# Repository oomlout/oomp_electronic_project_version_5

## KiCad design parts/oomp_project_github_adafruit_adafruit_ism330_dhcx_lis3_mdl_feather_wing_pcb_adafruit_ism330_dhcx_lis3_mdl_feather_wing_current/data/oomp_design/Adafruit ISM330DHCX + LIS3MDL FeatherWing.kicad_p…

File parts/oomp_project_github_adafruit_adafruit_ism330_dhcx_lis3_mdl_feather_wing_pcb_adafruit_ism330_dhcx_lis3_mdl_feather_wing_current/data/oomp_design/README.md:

# OOMP KiCad design copy

Open `Adafruit ISM330DHCX + LIS3MDL FeatherWing.kicad_pro` (or the `.kicad_pcb` / `.kicad_sch`) in KiCad. Local OOMP libraries are under `libraries/`. Original inputs are preserved in [../original/](../original/).

Only verified unchanged installed KiCad defaults were renamed. Modified, custom, unmatched and unavailable items remain unchanged. Soldering variants are never swapped during conversion. Existing pad coordinates, nets and UUIDs are preserved.

See [conversion_report.yaml](conversion_report.yaml) for every conversion and skip. Copy this directory before editing; regeneration refuses to overwrite edited design files.

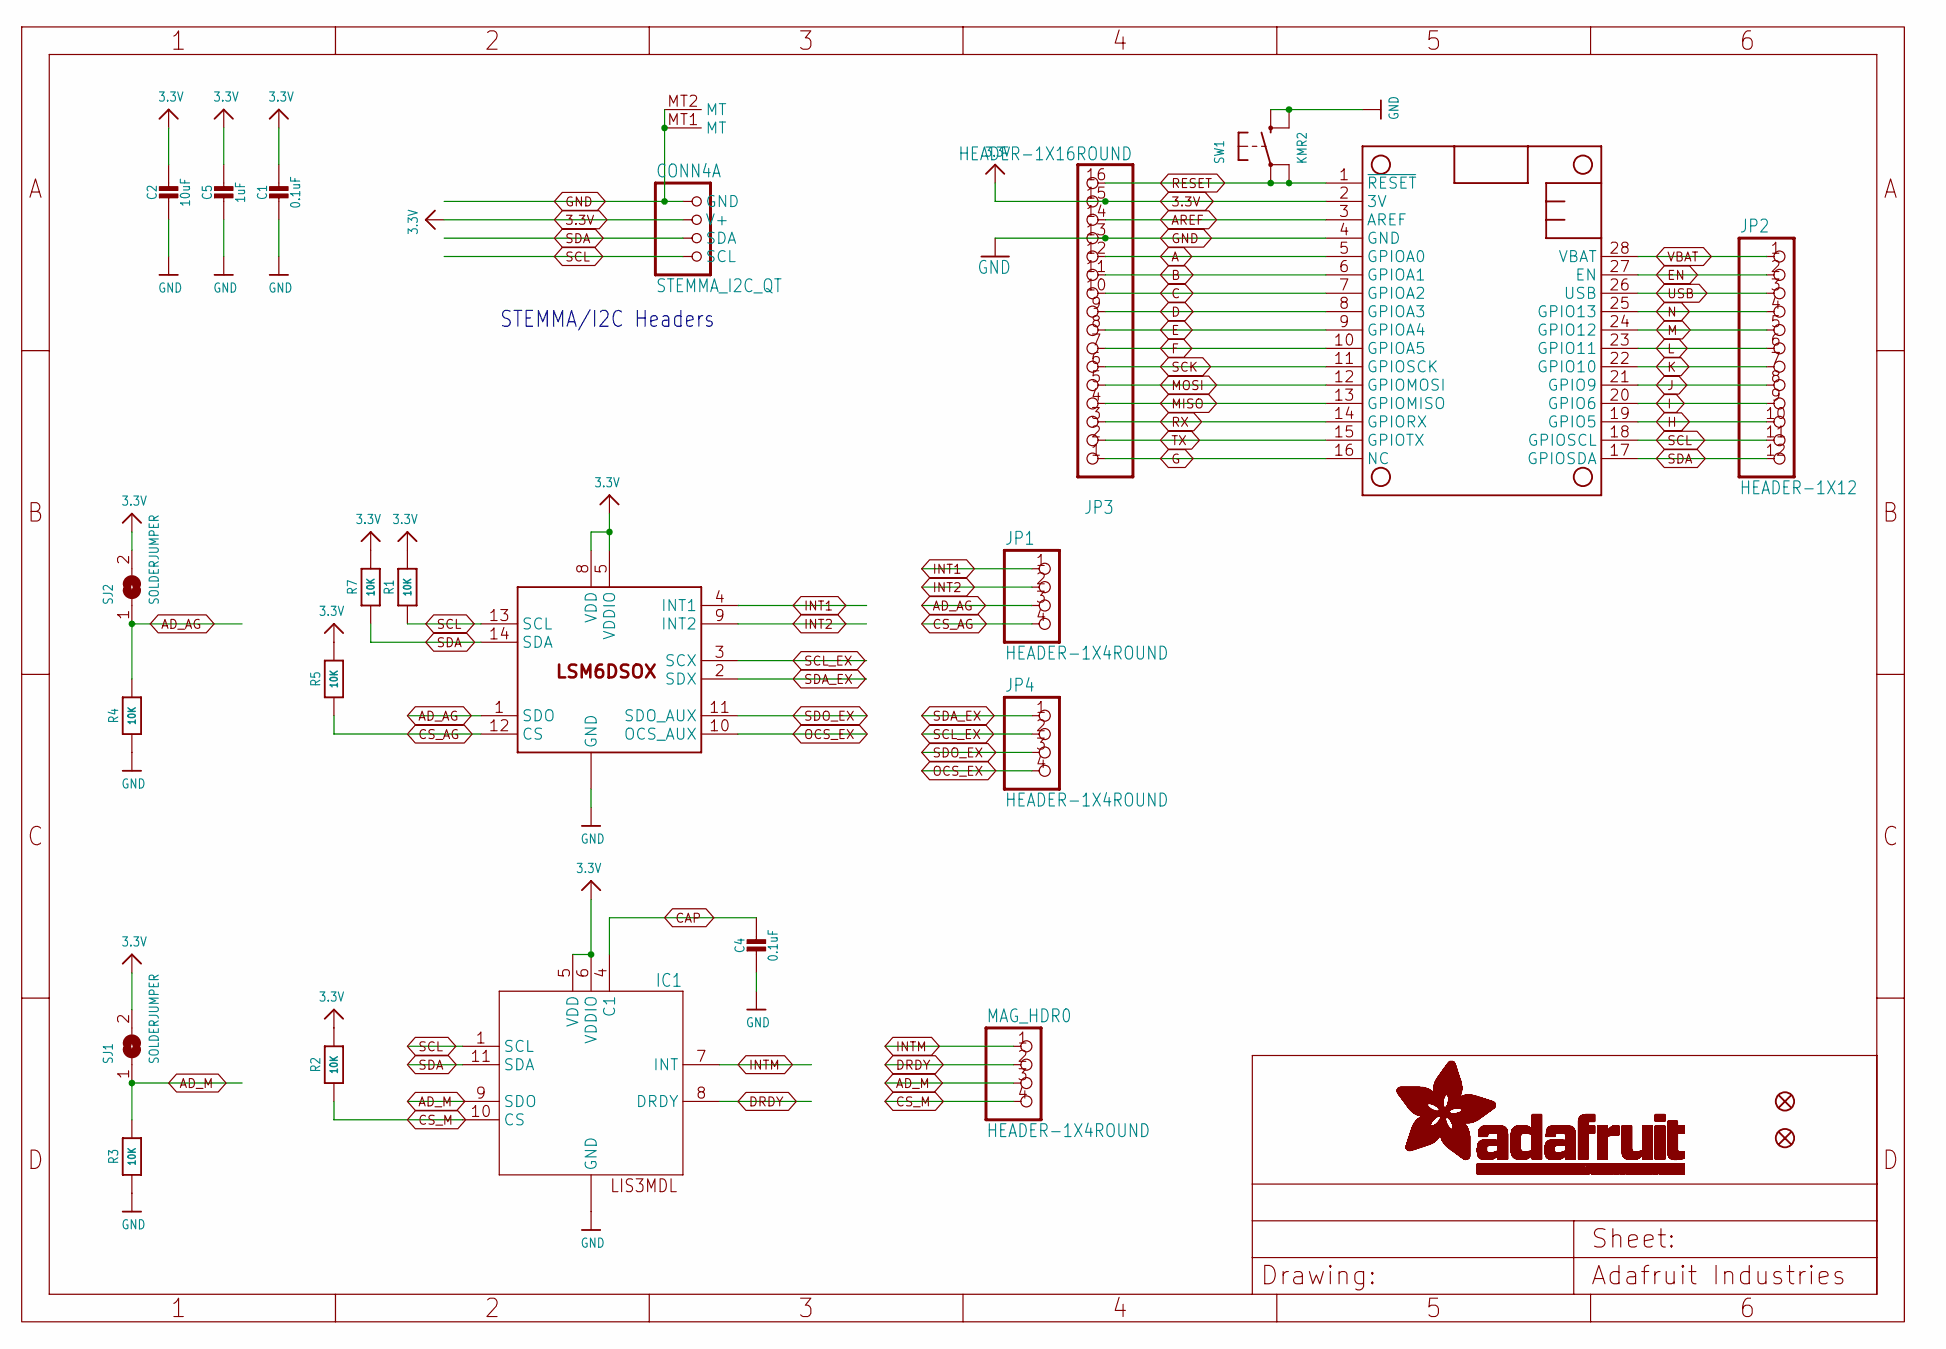
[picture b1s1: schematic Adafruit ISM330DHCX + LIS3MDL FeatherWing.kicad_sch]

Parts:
C1, C4: 0.1uF; 0603-NO
C2: 10uF; 0805-NO
C5: 1uF; 0603-NO
CONN4: STEMMA_I2C_QT; JST_SH4
FID1, FID2: FIDUCIAL_1MM
IC1: LIS3MDL; LGA12_2X2MM
JP1, JP4: HEADER-1X4ROUND; 1X04_ROUND
JP2: HEADER-1X12; 1X12_ROUND
JP3: HEADER-1X16ROUND; 1X16_ROUND
MAG_HDR0: HEADER-1X4ROUND; 1X04_ROUND
MS1: FEATHERWING
R1, R2, R3, R4, R5, R7: 10K; 0603-NO
SJ1, SJ2: SOLDERJUMPER; SOLDERJUMPER_ARROW_NOPASTE
SW1: KMR2; BTN_KMR2_4.6X2.8
U$35: LSM6DSOX; LGA-14L

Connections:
3.3V: C1.1, C2.1, C5.1, CONN4.2 (V+), IC1.5 (VDD), IC1.6 (VDDIO), JP3.15, MS1.2 (3V), R1.2, R2.2, R5.2, R7.2, SJ1.2, SJ2.2, U$35.5 (VDDIO), U$35.8 (VDD)
A: JP3.12, MS1.5 (GPIOA0)
AD_AG: JP1.3, R4.2, SJ2.1, U$35.1 (SDO)
AD_M: IC1.9 (SDO), MAG_HDR0.3, R3.2, SJ1.1
AREF: JP3.14, MS1.3 (AREF)
B: JP3.11, MS1.6 (GPIOA1)
C: JP3.10, MS1.7 (GPIOA2)
CAP: C4.1, IC1.4 (C1)
CS_AG: JP1.4, R5.1, U$35.12 (CS)
CS_M: IC1.10 (CS), MAG_HDR0.4, R2.1
D: JP3.9, MS1.8 (GPIOA3)
DRDY: IC1.8 (DRDY), MAG_HDR0.2
E: JP3.8, MS1.9 (GPIOA4)
EN: JP2.2, MS1.27 (EN)
F: JP3.7, MS1.10 (GPIOA5)
G: JP3.1, MS1.16 (NC)
GND: C1.2, C2.2, C4.2, C5.2, CONN4.1 (GND), CONN4.MT1 (MT), CONN4.MT2 (MT), IC1.2 (GND), IC1.3 (GND), IC1.12 (GND), JP3.13, MS1.4 (GND), R3.1, R4.1, SW1.B (S), SW1.B' (S1), U$35.6 (GND), U$35.7 (GND)
H: JP2.10, MS1.19 (GPIO5)
I: JP2.9, MS1.20 (GPIO6)
INT1: JP1.1, U$35.4 (INT1)
INT2: JP1.2, U$35.9 (INT2)
INTM: IC1.7 (INT), MAG_HDR0.1
J: JP2.8, MS1.21 (GPIO9)
K: JP2.7, MS1.22 (GPIO10)
L: JP2.6, MS1.23 (GPIO11)
M: JP2.5, MS1.24 (GPIO12)
MISO: JP3.4, MS1.13 (GPIOMISO)
MOSI: JP3.5, MS1.12 (GPIOMOSI)
N: JP2.4, MS1.25 (GPIO13)
OCS_EX: JP4.4, U$35.10 (OCS_AUX)
RESET: JP3.16, MS1.1 (~RESET), SW1.A, SW1.A' (P1)
RX: JP3.3, MS1.14 (GPIORX)
SCK: JP3.6, MS1.11 (GPIOSCK)
SCL: CONN4.4 (SCL), IC1.1 (SCL), JP2.11, MS1.18 (GPIOSCL), R1.1, U$35.13 (SCL)
SCL_EX: JP4.2, U$35.3 (SCX)
SDA: CONN4.3 (SDA), IC1.11 (SDA), JP2.12, MS1.17 (GPIOSDA), R7.1, U$35.14 (SDA)
SDA_EX: JP4.1, U$35.2 (SDX)
SDO_EX: JP4.3, U$35.11 (SDO_AUX)
TX: JP3.2, MS1.15 (GPIOTX)
USB: JP2.3, MS1.26 (USB)
VBAT: JP2.1, MS1.28 (VBAT)

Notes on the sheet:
STEMMA/I2C Headers

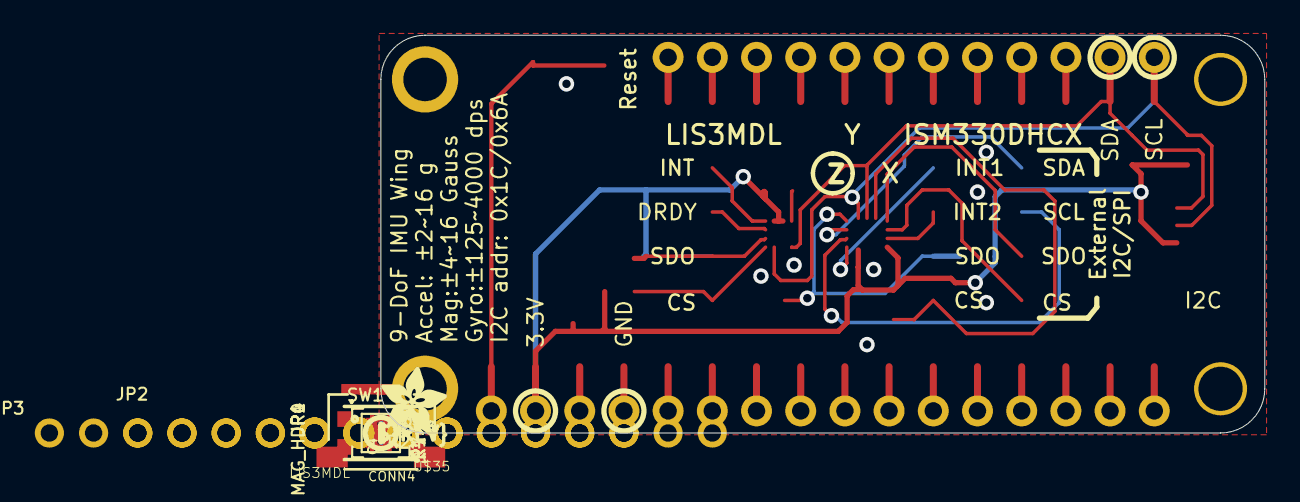
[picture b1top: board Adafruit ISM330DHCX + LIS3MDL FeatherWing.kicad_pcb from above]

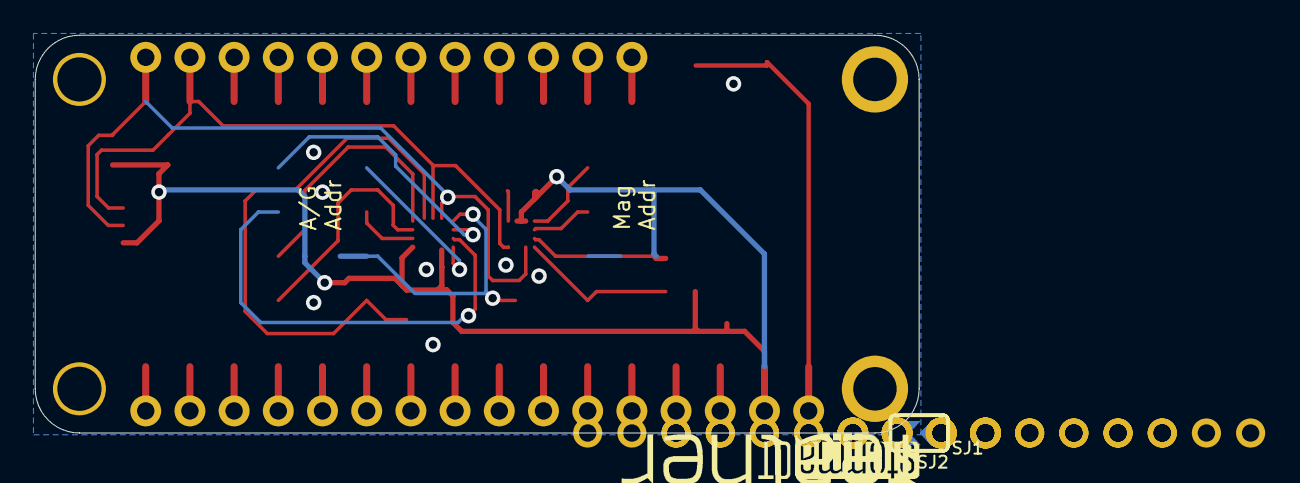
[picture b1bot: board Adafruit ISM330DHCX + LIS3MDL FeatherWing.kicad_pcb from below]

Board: 2 copper layers, 50.8 x 22.9 mm, 28 parts (4 on the bottom side), 41 nets.

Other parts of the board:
U$13: FEATHERLOGO_MED
U$31: STEMMAQT
U$50: ADAFRUIT_3.5MM
U$51: PCBFEAT-REV-040

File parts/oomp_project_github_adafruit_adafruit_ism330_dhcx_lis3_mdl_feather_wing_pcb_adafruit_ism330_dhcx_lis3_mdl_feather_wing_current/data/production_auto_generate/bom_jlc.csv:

Comment,Designator,Footprint,LCSC Part #
,"JP1,JP4,MAG_HDR0",Adafruit ISM330DHCX + LIS3MDL FeatherWing-import-fps:1X04_ROUND,C42431795
,JP2,Adafruit ISM330DHCX + LIS3MDL FeatherWing-import-fps:1X12_ROUND,C7501588
,JP3,Adafruit ISM330DHCX + LIS3MDL FeatherWing-import-fps:1X16_ROUND,C7501270
,U$50,Adafruit ISM330DHCX + LIS3MDL FeatherWing-import-fps:ADAFRUIT_3.5MM,
,U$13,Adafruit ISM330DHCX + LIS3MDL FeatherWing-import-fps:FEATHERLOGO_MED,
,U$51,Adafruit ISM330DHCX + LIS3MDL FeatherWing-import-fps:PCBFEAT-REV-040,
,U$31,Adafruit ISM330DHCX + LIS3MDL FeatherWing-import-fps:STEMMAQT,
0.1uF,"C1,C4",Adafruit ISM330DHCX + LIS3MDL FeatherWing-import-fps:0603-NO,C14663
10K,"R1,R2,R3,R4,R5,R7",Adafruit ISM330DHCX + LIS3MDL FeatherWing-import-fps:0603-NO,C98220
10uF,C2,Adafruit ISM330DHCX + LIS3MDL FeatherWing-import-fps:0805-NO,
1uF,C5,Adafruit ISM330DHCX + LIS3MDL FeatherWing-import-fps:0603-NO,C5673
FEATHERWING,MS1,Adafruit ISM330DHCX + LIS3MDL FeatherWing-import-fps:FEATHERWING,
KMR2,SW1,Adafruit ISM330DHCX + LIS3MDL FeatherWing-import-fps:BTN_KMR2_4.6X2.8,
LIS3MDL,IC1,Adafruit ISM330DHCX + LIS3MDL FeatherWing-import-fps:LGA12_2X2MM,
LSM6DSOX,U$35,Adafruit ISM330DHCX + LIS3MDL FeatherWing-import-fps:LGA-14L,
STEMMA_I2C_QT,CONN4,Adafruit ISM330DHCX + LIS3MDL FeatherWing-import-fps:JST_SH4,C160404

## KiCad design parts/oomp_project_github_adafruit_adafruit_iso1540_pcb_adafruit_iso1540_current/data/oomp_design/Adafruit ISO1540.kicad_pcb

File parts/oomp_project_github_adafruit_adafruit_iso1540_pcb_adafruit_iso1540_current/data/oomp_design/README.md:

# OOMP KiCad design copy

Open `Adafruit ISO1540.kicad_pro` (or the `.kicad_pcb` / `.kicad_sch`) in KiCad. Local OOMP libraries are under `libraries/`. Original inputs are preserved in [../original/](../original/).

Only verified unchanged installed KiCad defaults were renamed. Modified, custom, unmatched and unavailable items remain unchanged. Soldering variants are never swapped during conversion. Existing pad coordinates, nets and UUIDs are preserved.

See [conversion_report.yaml](conversion_report.yaml) for every conversion and skip. Copy this directory before editing; regeneration refuses to overwrite edited design files.

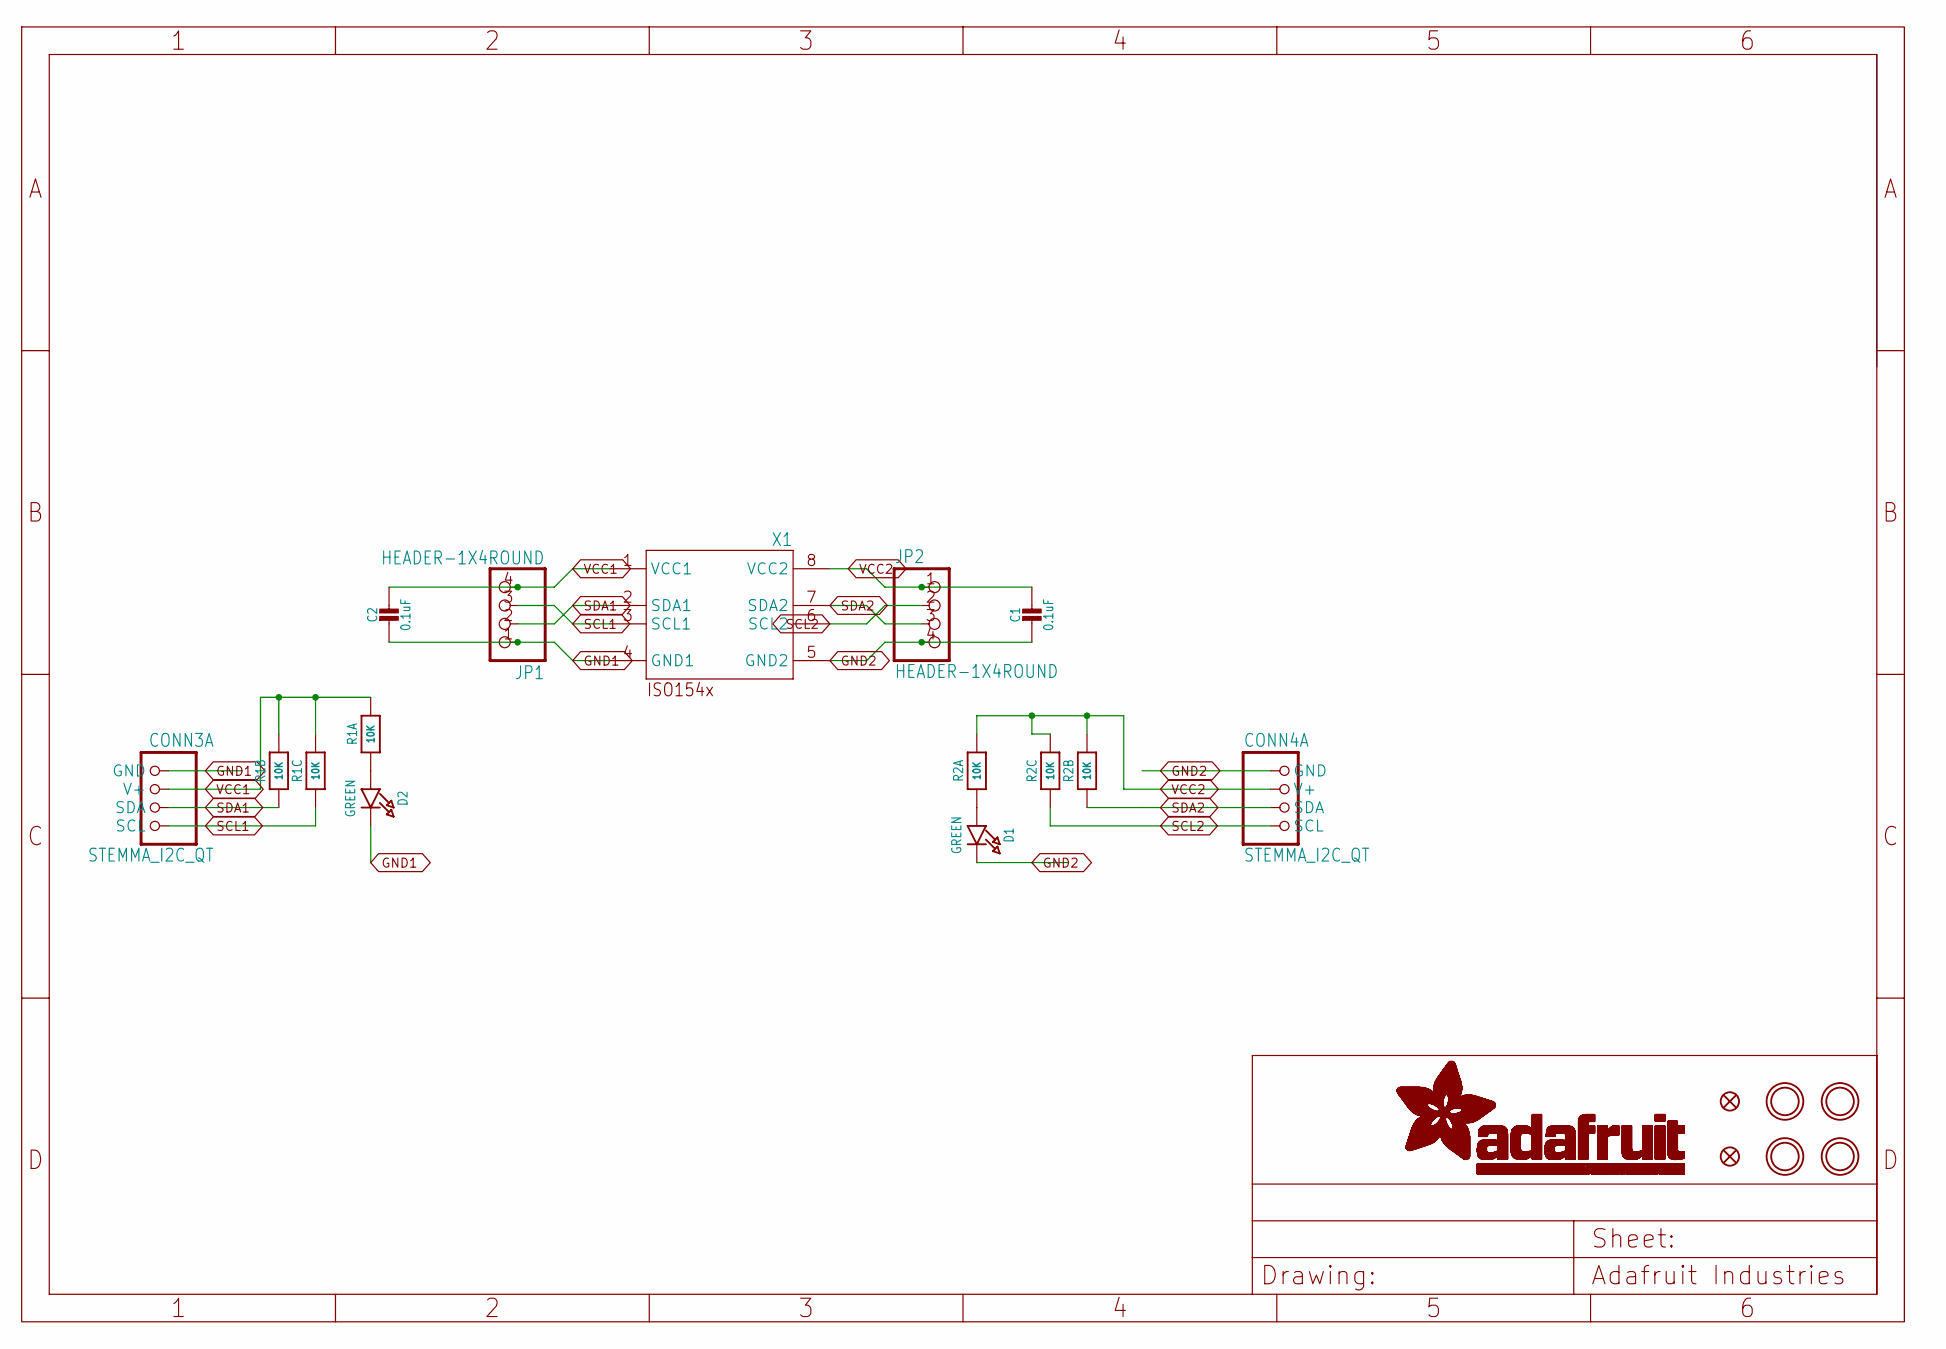
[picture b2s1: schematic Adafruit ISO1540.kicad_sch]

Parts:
C1, C2: 0.1uF; 0603-NO
CONN3, CONN4: STEMMA_I2C_QT; JST_SH4
D1, D2: GREEN; CHIPLED_0603_NOOUTLINE
FID3, FID4: FIDUCIAL_1MM
JP1, JP2: HEADER-1X4ROUND; 1X04_ROUND
R1, R2: 10K; RESPACK_4X0603
U$1, U$17, U$19, U$21: MOUNTINGHOLE2.5; MOUNTINGHOLE_2.5_PLATED
X1: ISO154X; SOIC8_150MIL

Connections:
GND1: C2.2, CONN3.1 (GND), D2.C, JP1.1, X1.4 (GND1)
GND2: C1.2, CONN4.1 (GND), D1.C, JP2.4, X1.5 (GND2)
unnamed: D2.A, R1.1
unnamed: D1.A, R2.1
SCL1: CONN3.4 (SCL), JP1.3, R1.3 (1), X1.3 (SCL1)
SCL2: CONN4.4 (SCL), JP2.2, R2.3 (1), X1.6 (SCL2)
SDA1: CONN3.3 (SDA), JP1.2, R1.2 (1), X1.2 (SDA1)
SDA2: CONN4.3 (SDA), JP2.3, R2.2 (1), X1.7 (SDA2)
VCC1: C2.1, CONN3.2 (V+), JP1.4, R1.6 (2), R1.7 (2), R1.8 (2), X1.1 (VCC1)
VCC2: C1.1, CONN4.2 (V+), JP2.1, R2.6 (2), R2.7 (2), R2.8 (2), X1.8 (VCC2)

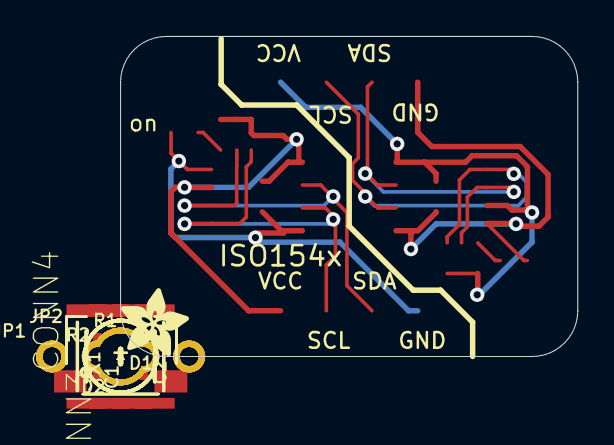
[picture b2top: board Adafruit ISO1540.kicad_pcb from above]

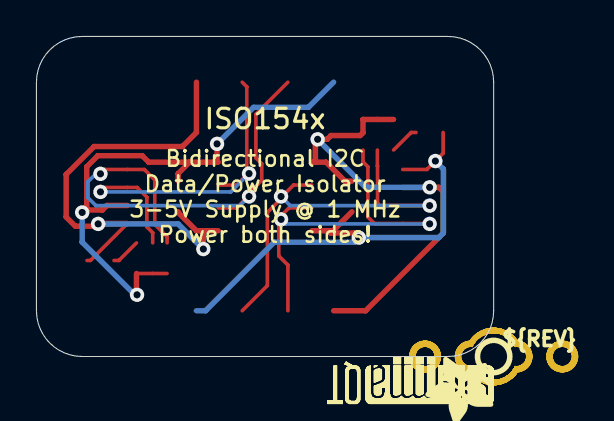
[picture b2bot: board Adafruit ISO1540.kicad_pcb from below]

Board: 2 copper layers, 25.4 x 17.8 mm, 22 parts (4 on the bottom side), 10 nets.

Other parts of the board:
U$2, U$22: ADAFRUIT_3.5MM
U$25: PCBFEAT-REV-040
U$30, U$31: STEMMAQT

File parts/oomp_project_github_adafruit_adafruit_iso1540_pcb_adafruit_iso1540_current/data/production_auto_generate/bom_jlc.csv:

Comment,Designator,Footprint,LCSC Part #
,"JP1,JP2",Adafruit ISO1540-import-fps:1X04_ROUND,C42431795
,"U$2,U$22",Adafruit ISO1540-import-fps:ADAFRUIT_3.5MM,
,U$25,Adafruit ISO1540-import-fps:PCBFEAT-REV-040,
,"U$30,U$31",Adafruit ISO1540-import-fps:STEMMAQT,
0.1uF,"C1,C2",Adafruit ISO1540-import-fps:0603-NO,C14663
10K,"R1,R2",Adafruit ISO1540-import-fps:RESPACK_4X0603,C98220
GREEN,"D1,D2",Adafruit ISO1540-import-fps:CHIPLED_0603_NOOUTLINE,
ISO154X,X1,Adafruit ISO1540-import-fps:SOIC8_150MIL,
STEMMA_I2C_QT,"CONN3,CONN4",Adafruit ISO1540-import-fps:JST_SH4,C160404

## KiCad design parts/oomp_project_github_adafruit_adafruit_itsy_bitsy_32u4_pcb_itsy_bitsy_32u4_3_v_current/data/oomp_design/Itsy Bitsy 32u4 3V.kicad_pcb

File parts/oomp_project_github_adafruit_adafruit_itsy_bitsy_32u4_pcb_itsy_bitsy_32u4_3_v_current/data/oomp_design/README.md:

# OOMP KiCad design copy

Open `Itsy Bitsy 32u4 3V.kicad_pro` (or the `.kicad_pcb` / `.kicad_sch`) in KiCad. Local OOMP libraries are under `libraries/`. Original inputs are preserved in [../original/](../original/).

Only verified unchanged installed KiCad defaults were renamed. Modified, custom, unmatched and unavailable items remain unchanged. Soldering variants are never swapped during conversion. Existing pad coordinates, nets and UUIDs are preserved.

See [conversion_report.yaml](conversion_report.yaml) for every conversion and skip. Copy this directory before editing; regeneration refuses to overwrite edited design files.

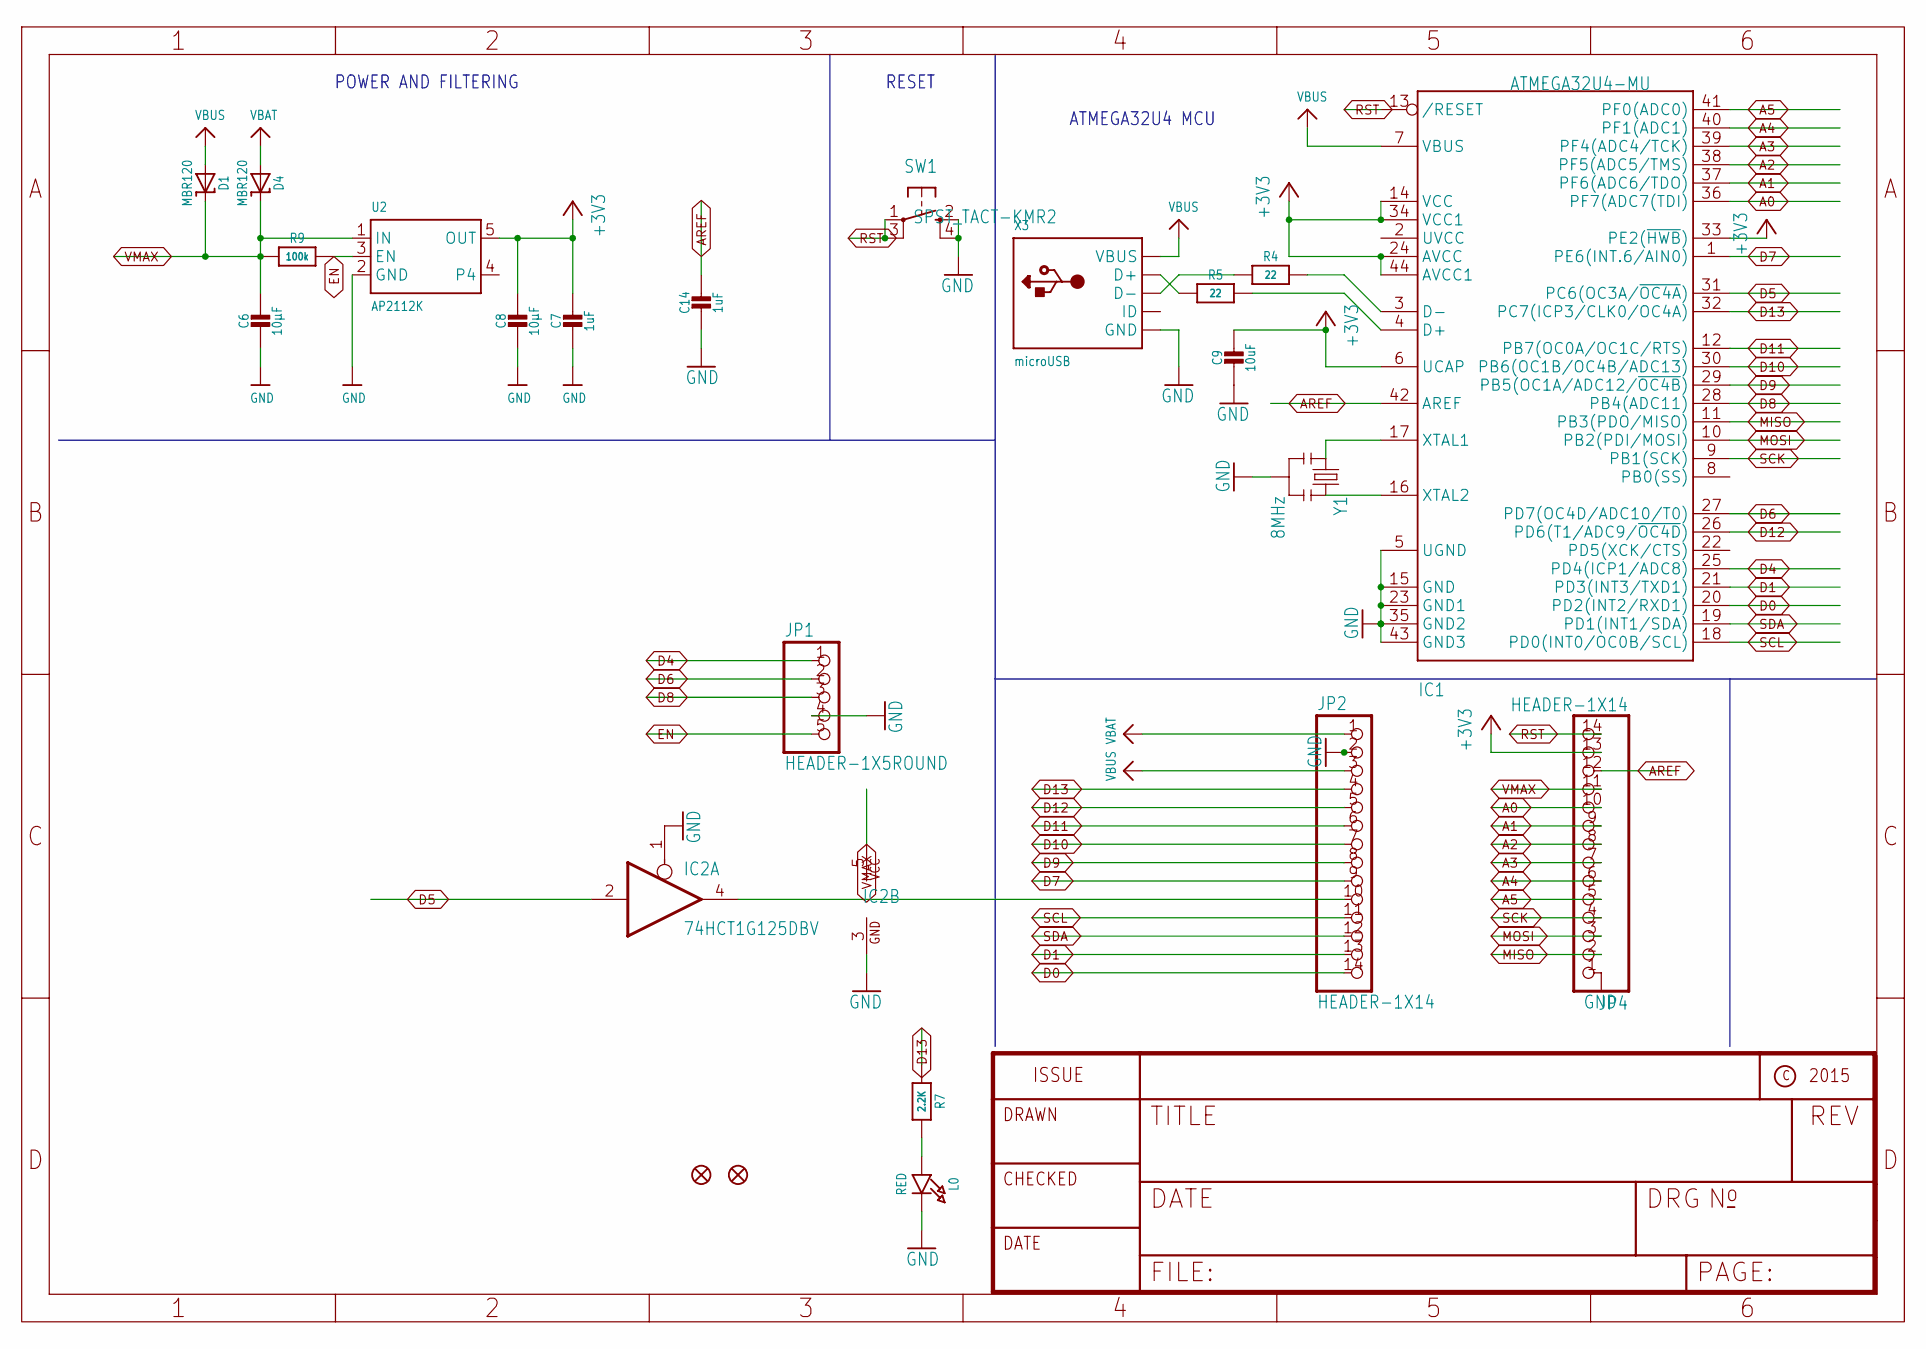
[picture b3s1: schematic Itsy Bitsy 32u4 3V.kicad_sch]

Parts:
C6, C8: 10µF; 0805-NO
C7, C14: 1uF; 0603-NO
C9: 10uF; 0805-NO
D1, D4: MBR120; SOD-123
IC1: ATMEGA32U4-MU; TQFN44_7MM
IC2: 74HCT1G125DBV; SOT23-5
JP1: HEADER-1X5ROUND; 1X05_ROUND
JP2, JP4: HEADER-1X14; 1X14_ROUND70
L0: RED; CHIPLED_0805_NOOUTLINE
R4, R5: 22; 0603-NO
R7: 2.2K; 0603-NO
R9: 100k; 0603-NO
SW1: SPST_TACT-KMR2; KMR2
U2: AP2112K; SOT23-5
U$34, U$35: FIDUCIAL""; FIDUCIAL_1MM
X3: microUSB; 4UCONN_20329_V2
Y1: 8MHz; RESONATOR-SMD

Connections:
+3V3: C7.1, C8.1, C9.1, IC1.6 (UCAP), IC1.14 (VCC), IC1.24 (AVCC), IC1.33 (PE2(~HWB)), IC1.34 (VCC1), IC1.44 (AVCC1), JP4.13, U2.5 (OUT)
A0: IC1.36 (PF7(ADC7(TDI)), JP4.10
A1: IC1.37 (PF6(ADC6/TDO)), JP4.9
A2: IC1.38 (PF5(ADC5/TMS)), JP4.8
A3: IC1.39 (PF4(ADC4/TCK)), JP4.7
A4: IC1.40 (PF1(ADC1)), JP4.6
A5: IC1.41 (PF0(ADC0)), JP4.5
AREF: C14.1, IC1.42 (AREF), JP4.12
D0: IC1.20 (PD2(INT2/RXD1)), JP2.14
D1: IC1.21 (PD3(INT3/TXD1)), JP2.13
D4: IC1.25 (PD4(ICP1/ADC8)), JP1.1
D5: IC1.31 (PC6(OC3A/~OC4A)), IC2.2 (I)
D5_OUT: IC2.4 (O), JP2.10
D6: IC1.27 (PD7(OC4D/ADC10/T0)), JP1.2
D7: IC1.1 (PE6(INT.6/AIN0)), JP2.9
D8: IC1.28 (PB4(ADC11)), JP1.3
D9: IC1.29 (PB5(OC1A/ADC12/~OC4B)), JP2.8
D10: IC1.30 (PB6(OC1B/OC4B/ADC13)), JP2.7
D11: IC1.12 (PB7(OC0A/OC1C/RTS)), JP2.6
D12: IC1.26 (PD6(T1/ADC9/~OC4D)), JP2.5
D13: IC1.32 (PC7(ICP3/CLK0/OC4A)), JP2.4, R7.1
D+: IC1.4 (D+), R5.2
D-: IC1.3 (D-), R4.2
EN: JP1.5, R9.2, U2.3 (EN)
GND: C6.2, C7.2, C8.2, C9.2, C14.2, IC1.5 (UGND), IC1.15 (GND), IC1.23 (GND1), IC1.35 (GND2), IC1.43 (GND3), IC2.1 (OE), IC2.3 (GND), JP1.4, JP2.2, JP4.1, L0.C, SW1.2 (S), SW1.4 (S1), U2.2 (GND), X3.BASE@1 (GND), X3.BASE@2 (GND), X3.GND, X3.SPRT@1 (GND), X3.SPRT@2 (GND), X3.SPRT@3 (GND), X3.SPRT@4 (GND), Y1.2
MISO: IC1.11 (PB3(PDO/MISO)), JP4.2
MOSI: IC1.10 (PB2(PDI/MOSI)), JP4.3
unnamed: L0.A, R7.2
unnamed: IC1.16 (XTAL2), Y1.3
unnamed: IC1.17 (XTAL1), Y1.1
unnamed: R5.1, X3.D+
unnamed: R4.1, X3.D-
RST: IC1.13 (/RESET), JP4.14, SW1.1, SW1.3 (P1)
SCK: IC1.9 (PB1(SCK)), JP4.4
SCL: IC1.18 (PD0(INT0/OC0B/SCL)), JP2.11
SDA: IC1.19 (PD1(INT1/SDA)), JP2.12
VBAT: D4.A, JP2.1
VBUS: D1.A, IC1.7 (VBUS), JP2.3, X3.VBUS
VMAX: C6.1, D1.C, D4.C, IC2.5 (VCC), JP4.11, R9.1, U2.1 (IN)

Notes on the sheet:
POWER AND FILTERING
RESET
ATMEGA32U4 MCU

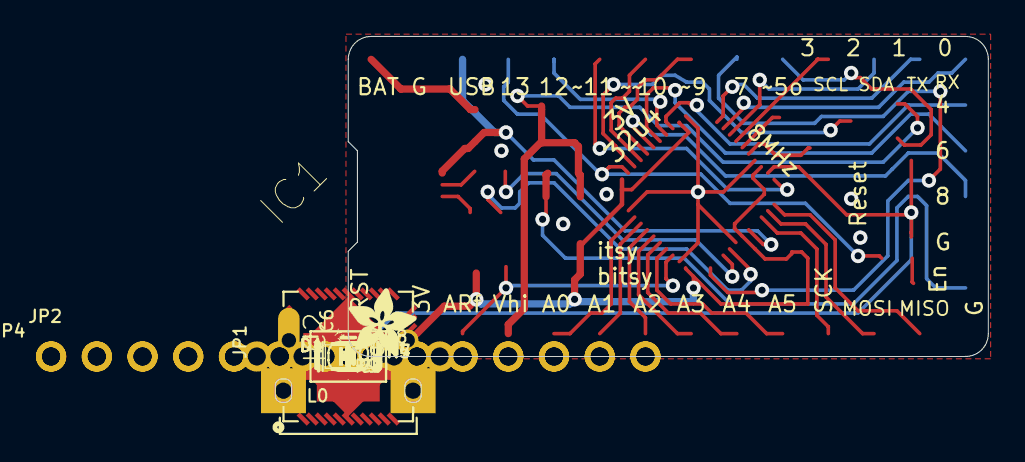
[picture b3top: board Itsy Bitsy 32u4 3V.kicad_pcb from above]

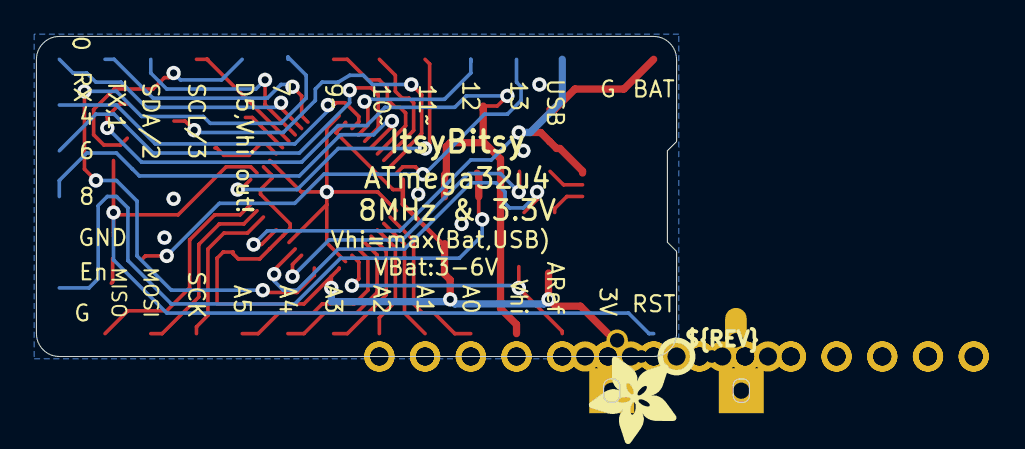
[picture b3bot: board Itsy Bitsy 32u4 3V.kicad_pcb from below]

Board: 2 copper layers, 35.6 x 17.8 mm, 26 parts (2 on the bottom side), 39 nets.

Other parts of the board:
U$2: PCBFEAT-REV-040
U$4: ADAFRUIT_5MM
U$7: ADAFRUIT_3.5MM

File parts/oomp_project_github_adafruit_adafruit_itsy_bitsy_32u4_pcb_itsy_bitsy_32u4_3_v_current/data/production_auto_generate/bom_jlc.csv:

Comment,Designator,Footprint,LCSC Part #
,JP1,Itsy Bitsy 32u4 3V-import-fps:1X05_ROUND,C42431835
,"JP2,JP4",Itsy Bitsy 32u4 3V-import-fps:1X14_ROUND70,C2905490
,U$7,Itsy Bitsy 32u4 3V-import-fps:ADAFRUIT_3.5MM,
,U$4,Itsy Bitsy 32u4 3V-import-fps:ADAFRUIT_5MM,
,U$2,Itsy Bitsy 32u4 3V-import-fps:PCBFEAT-REV-040,
100k,R9,Itsy Bitsy 32u4 3V-import-fps:0603-NO,C25803
10uF,C9,Itsy Bitsy 32u4 3V-import-fps:0805-NO,
10µF,"C6,C8",Itsy Bitsy 32u4 3V-import-fps:0805-NO,
1uF,"C7,C14",Itsy Bitsy 32u4 3V-import-fps:0603-NO,C5673
2.2K,R7,Itsy Bitsy 32u4 3V-import-fps:0603-NO,C4190
22,"R4,R5",Itsy Bitsy 32u4 3V-import-fps:0603-NO,C23345
74HCT1G125DBV,IC2,Itsy Bitsy 32u4 3V-import-fps:SOT23-5,
8MHz,Y1,Itsy Bitsy 32u4 3V-import-fps:RESONATOR-SMD,
AP2112K,U2,Itsy Bitsy 32u4 3V-import-fps:SOT23-5,
ATMEGA32U4-MU,IC1,Itsy Bitsy 32u4 3V-import-fps:TQFN44_7MM,
"FIDUCIAL""""","U$34,U$35",Itsy Bitsy 32u4 3V-import-fps:FIDUCIAL_1MM,
MBR120,"D1,D4",Itsy Bitsy 32u4 3V-import-fps:SOD-123,
microUSB,X3,Itsy Bitsy 32u4 3V-import-fps:4UCONN_20329_V2,
RED,L0,Itsy Bitsy 32u4 3V-import-fps:CHIPLED_0805_NOOUTLINE,
SPST_TACT-KMR2,SW1,Itsy Bitsy 32u4 3V-import-fps:KMR2,

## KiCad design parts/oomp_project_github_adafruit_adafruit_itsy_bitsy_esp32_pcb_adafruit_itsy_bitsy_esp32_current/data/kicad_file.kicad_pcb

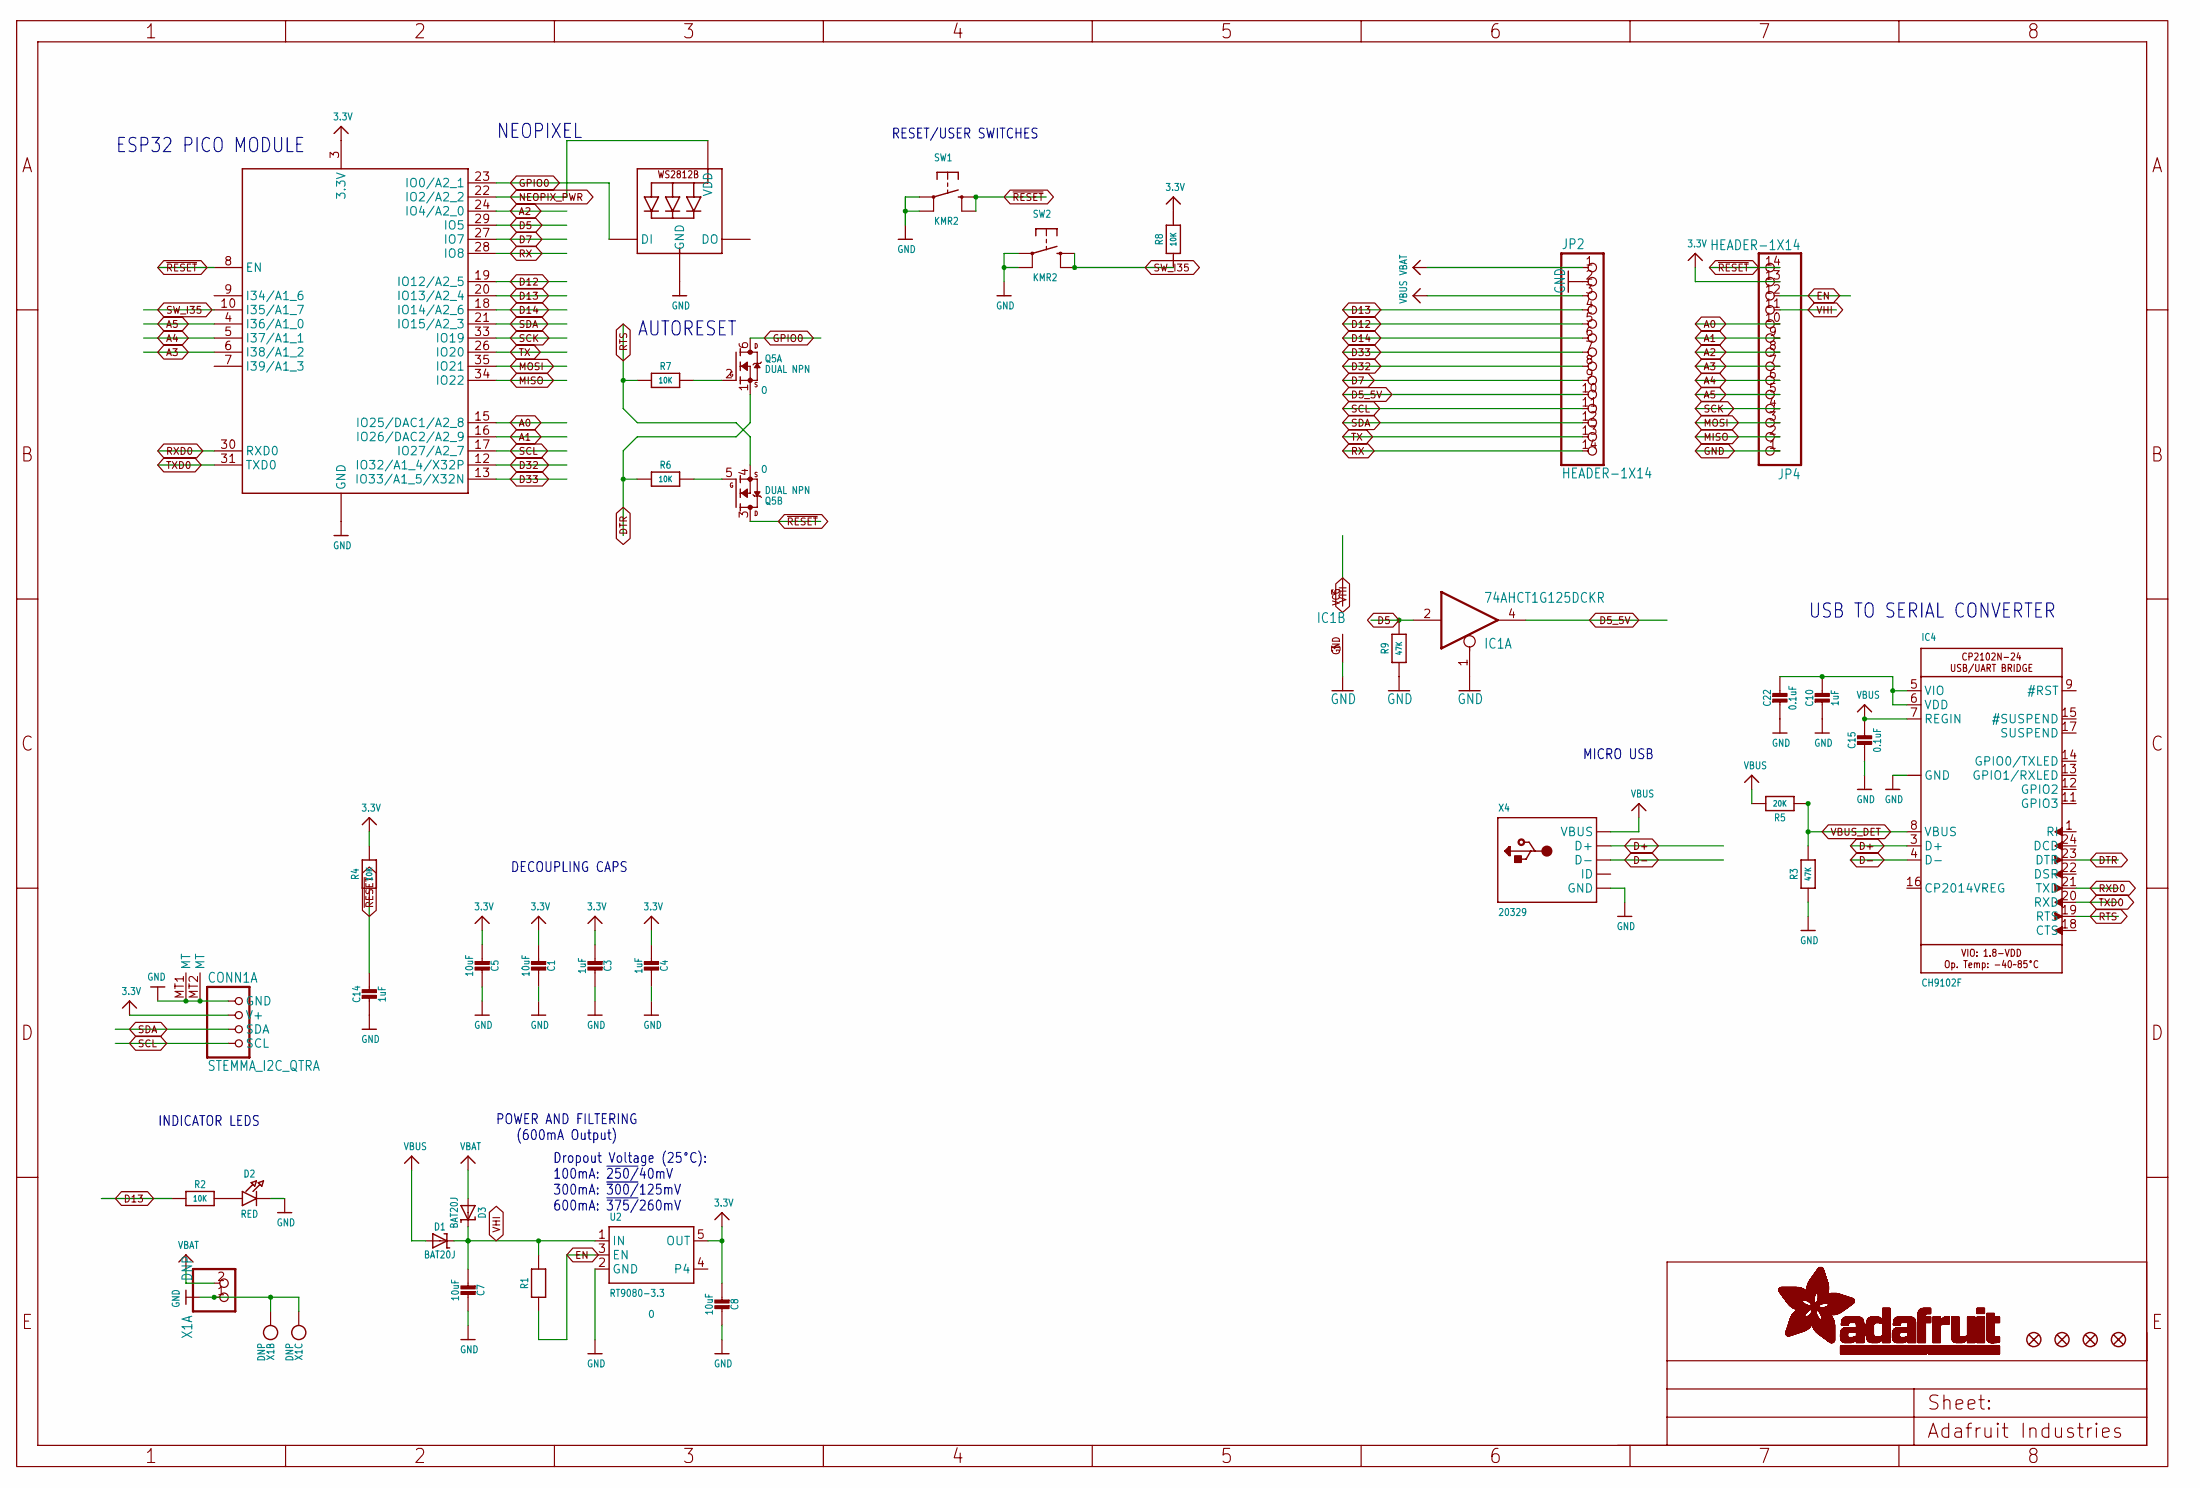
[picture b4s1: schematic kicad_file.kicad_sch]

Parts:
C1, C5, C7, C8: 10uF; 0805-NO
C3, C4, C10, C14: 1uF; 0603-NO
C15, C22: 0.1uF; 0603-NO
CONN1: STEMMA_I2C_QTRA; JST_SH4_RA; LCSC C145961
D1, D3: BAT20J; SOD-323
D2: RED; CHIPLED_0603_NOOUTLINE
FID1, FID2, FID3, FID4: FIDUCIAL_1MM
IC1: 74AHCT1G125DCKR; SC70-5
IC4: CH9102F; QFN24_4MM_SMSC; JLC_ROTATION 270
JP2, JP4: HEADER-1X14; 1X14_ROUND70
LED2: WS2812B_SK6805_1515; SK6805_1515; LCSC C2890035
Q5: DUAL NPN; SOT363; JLC_ROTATION 0
R1, R2, R4, R6, R7, R8: 10K; 0603-NO
R3, R9: 47K; 0603-NO
R5: 20K; 0603-NO
SW1, SW2: KMR2; BTN_RKB2_4.6X2.8
U2: RT9080-3.3; SOT23-5; JLC_ROTATION 0
X1: DNP; JSTPH2_BATT; LCSC C47647
X3: ESP32-PICO-MINI-02MINI; ESP32-PICO-MINI
X4: 20329; 4UCONN_20329_SLIM

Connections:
3.3V: C1.2, C3.2, C4.2, C5.2, C8.2, CONN1.2 (V+), JP4.13, R4.2, R8.2, U2.5 (OUT), X3.3 (3.3V)
3.45V: C10.1, C22.1, IC4.5 (VIO), IC4.6 (VDD)
A0: JP4.10, X3.15 (IO25/DAC1/A2_8)
A1: JP4.9, X3.16 (IO26/DAC2/A2_9)
A2: JP4.8, X3.24 (IO4/A2_0)
A3: JP4.7, X3.6 (I38/A1_2)
A4: JP4.6, X3.5 (I37/A1_1)
A5: JP4.5, X3.4 (I36/A1_0)
D5: IC1.2 (I), R9.2, X3.29 (IO5)
D5_5V: IC1.4 (O), JP2.10
D7: JP2.9, X3.27 (IO7)
D12: JP2.5, X3.19 (IO12/A2_5)
D13: JP2.4, R2.1, X3.20 (IO13/A2_4)
D14: JP2.6, X3.18 (IO14/A2_6)
D32: JP2.8, X3.12 (IO32/A1_4/X32P)
D33: JP2.7, X3.13 (IO33/A1_5/X32N)
D+: IC4.3 (D+), X4.D+
D-: IC4.4 (D-), X4.D-
DTR: IC4.23 (DTR), Q5.1 (S), R6.1
EN: JP4.12, R1.1, U2.3 (EN)
GND: C1.1, C3.1, C4.1, C5.1, C7.1, C8.1, C10.2, C14.2, C15.2, C22.2, CONN1.1 (GND), CONN1.MT1 (MT), CONN1.MT2 (MT), D2.C, IC1.1 (OE), IC1.3 (GND), IC4.2 (GND), IC4.THERM (GND), JP2.2, JP4.1, LED2.4 (GND), R3.1, R9.1, SW1.A, SW1.A' (P1), SW2.A, SW2.A' (P1), U2.2 (GND), X1.1, X1.NC1, X1.NC2, X3.1 (GND), X3.2 (GND), X3.11 (GND), X3.14 (GND), X3.36 (GND), X3.37 (GND), X3.38 (GND), X3.39 (GND), X3.40 (GND), X3.41 (GND), X3.42 (GND), X3.43 (GND), X3.44 (GND), X3.45 (GND), X3.46 (GND), X3.47 (GND), X3.48 (GND), X3.49 (GND), X3.50 (GND), X3.51 (GND), X3.52 (GND), X3.53 (GND), X3.54 (GND), X3.55 (GND), X3.56 (GND), X3.57 (GND), X3.58 (GND), X3.59 (GND), X3.60 (GND), X3.61 (GND), X4.BASE@1 (GND), X4.BASE@2 (GND), X4.GND, X4.SPRT@1 (GND), X4.SPRT@2 (GND), X4.SPRT@3 (GND), X4.SPRT@4 (GND)
GPIO0: LED2.1 (DI), Q5.6 (D), X3.23 (IO0/A2_1)
MISO: JP4.2, X3.34 (IO22)
MOSI: JP4.3, X3.35 (IO21)
unnamed: D2.A, R2.2
unnamed: Q5.5 (G), R6.2
unnamed: Q5.2 (G), R7.2
NEOPIX_PWR: LED2.2 (VDD), X3.22 (IO2/A2_2)
RTS: IC4.19 (RTS), Q5.4 (S), R7.1
RX: JP2.14, X3.28 (IO8)
RXD0: IC4.21 (TXD), X3.30 (RXD0)
SCK: JP4.4, X3.33 (IO19)
SCL: CONN1.4 (SCL), JP2.11, X3.17 (IO27/A2_7)
SDA: CONN1.3 (SDA), JP2.12, X3.21 (IO15/A2_3)
SW_I35: R8.1, SW2.B (S), SW2.B' (S1), X3.10 (I35/A1_7)
TX: JP2.13, X3.26 (IO20)
TXD0: IC4.20 (RXD), X3.31 (TXD0)
VBAT: D3.A, JP2.1, X1.2
VBUS: C15.1, D1.A, IC4.7 (REGIN), JP2.3, R5.2, X4.VBUS
VBUS_DET: IC4.8 (VBUS), R3.2, R5.1
VHI: C7.2, D1.C, D3.C, IC1.5 (VCC), JP4.11, R1.2, U2.1 (IN)
~RESET: C14.1, JP4.14, Q5.3 (D), R4.1, SW1.B (S), SW1.B' (S1), X3.8 (EN)

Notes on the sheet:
AUTORESET
MICRO USB
Dropout Voltage (25°C): 100mA: ~{250/}40mV 300mA: ~{300/}125mV 600mA: ~{375/}260mV
POWER AND FILTERING (600mA Output)
RESET/USER SWITCHES
ESP32 PICO MODULE
INDICATOR LEDS
DECOUPLING CAPS
USB TO SERIAL CONVERTER
NEOPIXEL
